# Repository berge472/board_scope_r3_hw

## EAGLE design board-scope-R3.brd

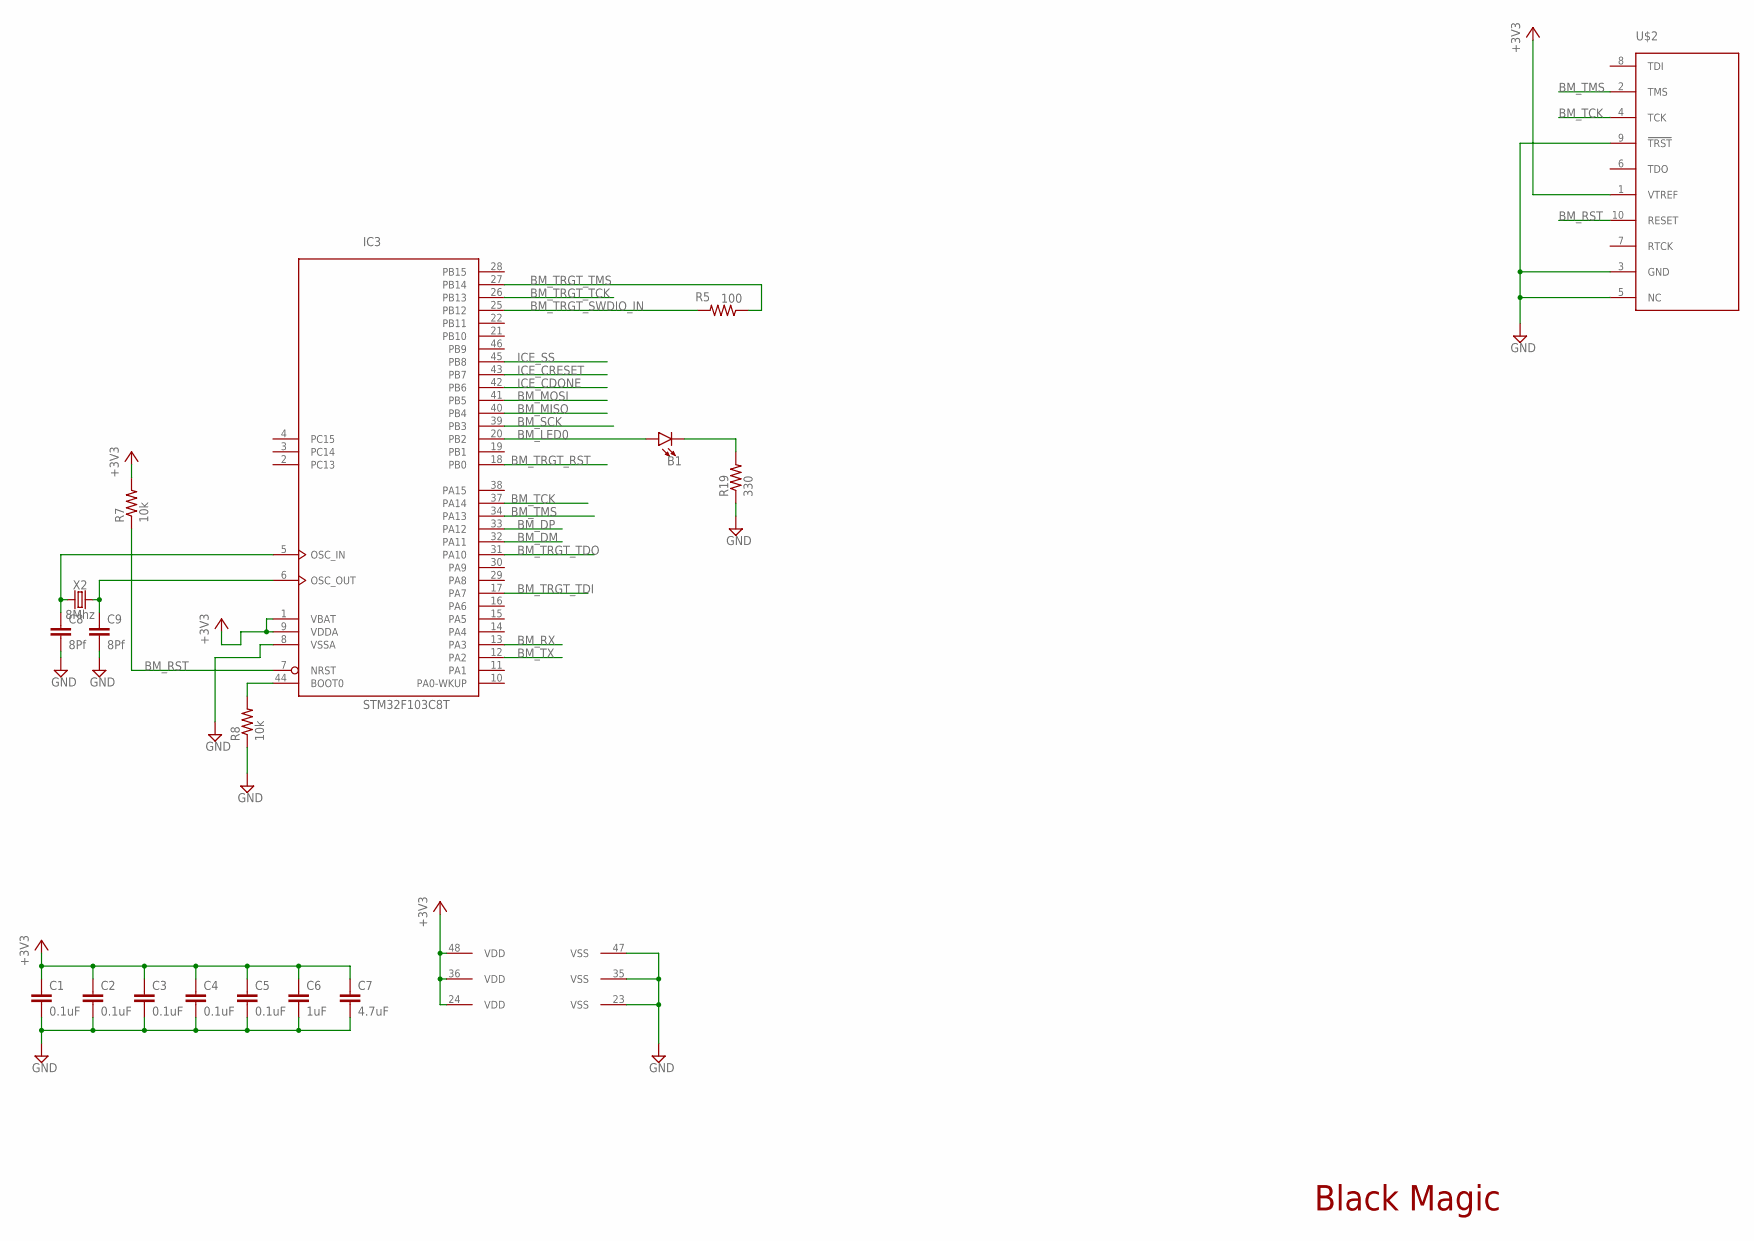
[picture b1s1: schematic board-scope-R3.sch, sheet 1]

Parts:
B1: LED0603; LED-0603
C1, C2, C3, C4, C5: 0.1uF; C0603K
C6: 1uF; C0603K
C7: 4.7uF; C0603K
C8, C9: 8Pf; C0603K
IC3: STM32F103C8T; LQFP48
R5: 100; R0603
R7, R8: 10k; R0603
R19: 330; R0603
U$2: TC2050-NL-MCP-NL; TC2030-MCP-NL
X2: 8Mhz; CRYSTAL-SMD-5X3.2-4PAD

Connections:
+3V3: C1.1, C2.1, C3.1, C4.1, C5.1, C6.1, C7.1, IC3.1 (VBAT), IC3.9 (VDDA), IC3.24 (VDD), IC3.36 (VDD), IC3.48 (VDD), R7.2, U$2.1 (VTREF); also elsewhere on the board
BM_DM: IC3.32 (PA11); also elsewhere on the board
BM_DP: IC3.33 (PA12); also elsewhere on the board
BM_LED0: B1.A, IC3.20 (PB2)
BM_MISO: IC3.40 (PB4); also elsewhere on the board
BM_MOSI: IC3.41 (PB5); also elsewhere on the board
BM_RST: IC3.7 (NRST), R7.1, U$2.10 (RESET); also elsewhere on the board
BM_RX: IC3.13 (PA3); also elsewhere on the board
BM_SCK: IC3.39 (PB3); also elsewhere on the board
BM_TCK: IC3.37 (PA14), U$2.4 (TCK); also elsewhere on the board
BM_TMS: IC3.34 (PA13), U$2.2 (TMS); also elsewhere on the board
BM_TRGT_RST: IC3.18 (PB0); also elsewhere on the board
BM_TRGT_SWDIO_IN: IC3.25 (PB12), R5.2
BM_TRGT_TCK: IC3.26 (PB13); also elsewhere on the board
BM_TRGT_TDI: IC3.17 (PA7); also elsewhere on the board
BM_TRGT_TDO: IC3.31 (PA10); also elsewhere on the board
BM_TRGT_TMS: IC3.27 (PB14), R5.1; also elsewhere on the board
BM_TX: IC3.12 (PA2); also elsewhere on the board
GND: C1.2, C2.2, C3.2, C4.2, C5.2, C6.2, C7.2, C8.2, C9.2, IC3.8 (VSSA), IC3.23 (VSS), IC3.35 (VSS), IC3.47 (VSS), R8.1, R19.1, U$2.3 (GND), U$2.5 (NC), U$2.9 (!TRST); also elsewhere on the board
ICE_CDONE: IC3.42 (PB6); also elsewhere on the board
ICE_CRESET: IC3.43 (PB7); also elsewhere on the board
ICE_SS: IC3.45 (PB8); also elsewhere on the board
unnamed: IC3.44 (BOOT0), R8.2
unnamed: C8.1, IC3.5 (OSC_IN), X2.1
unnamed: C9.1, IC3.6 (OSC_OUT), X2.3 (2)
unnamed: B1.C, R19.2

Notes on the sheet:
Black Magic

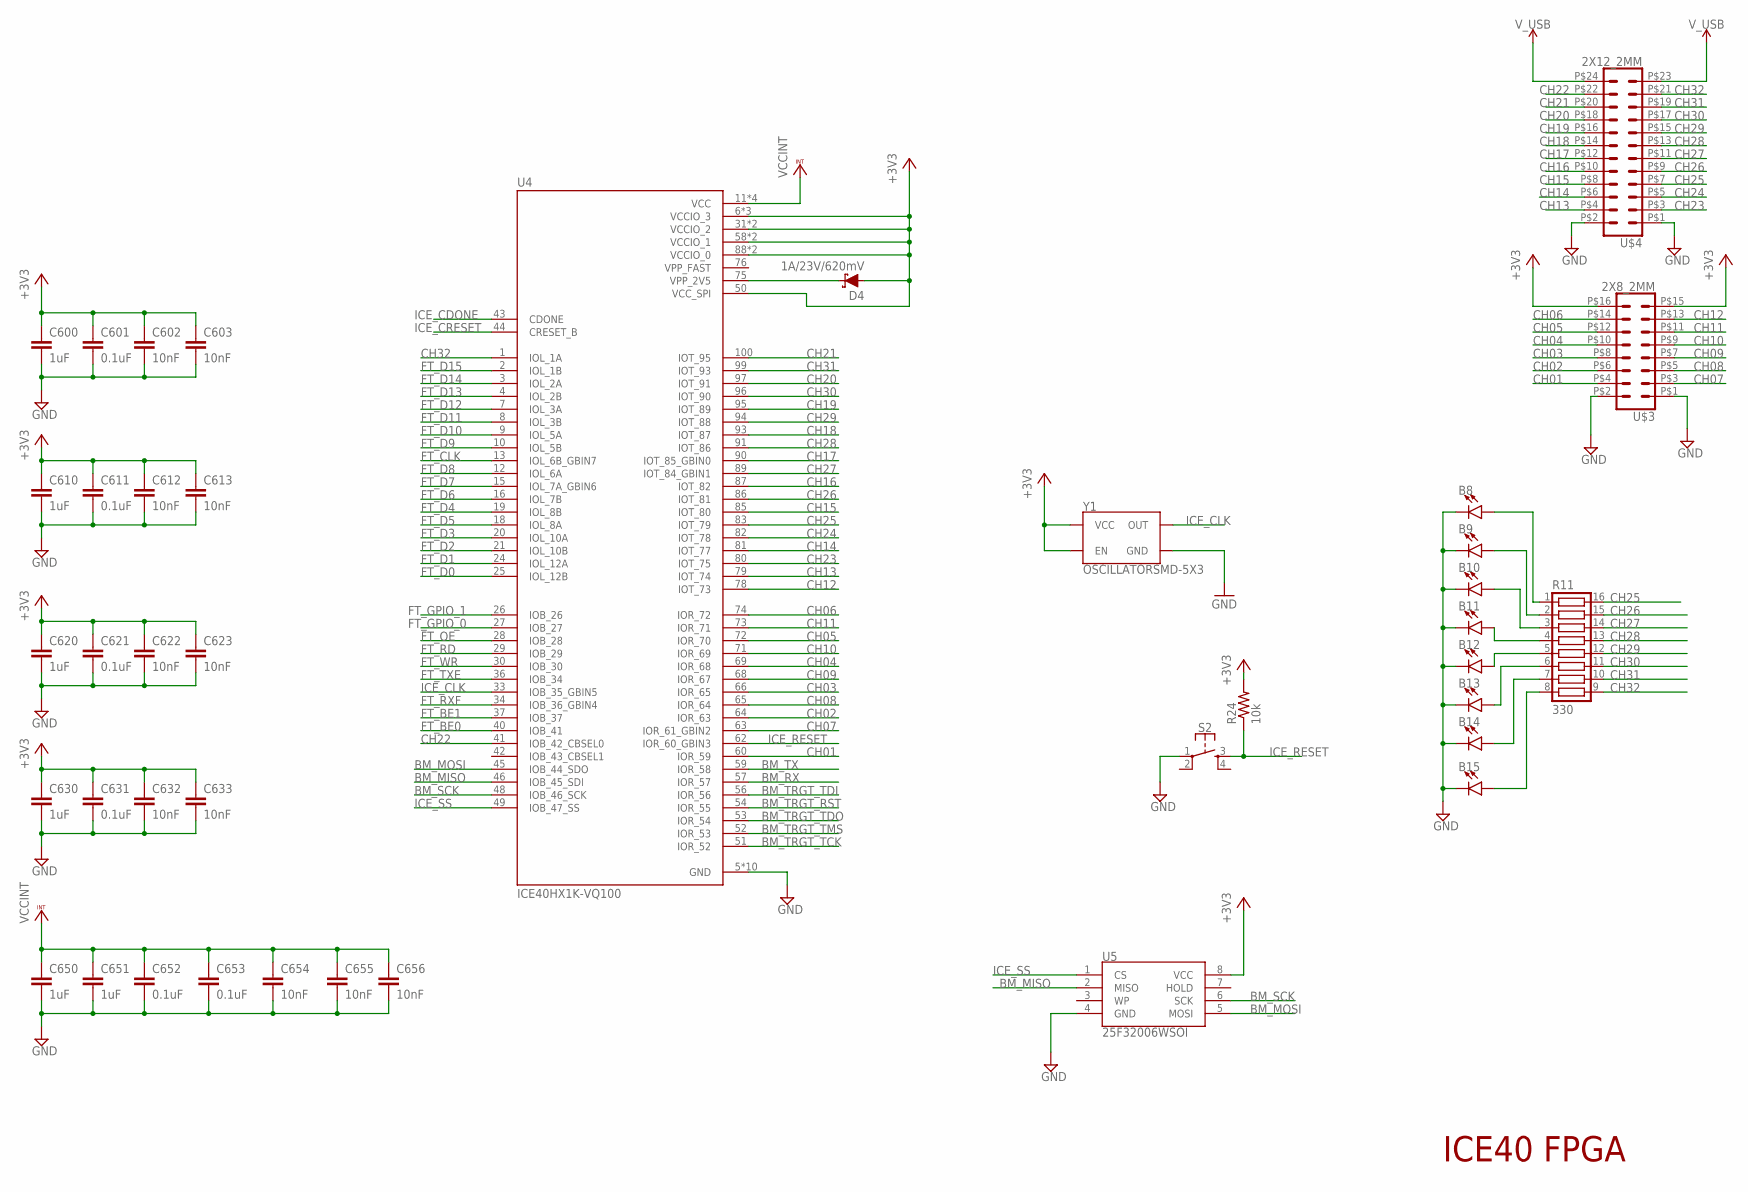
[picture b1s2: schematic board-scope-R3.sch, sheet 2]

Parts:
B8, B9, B10, B11, B12, B13, B14, B15: LED0603; LED-0603
C600, C610, C620, C630, C650, C651: 1uF; C0603K
C601, C611, C621, C631, C652, C653: 0.1uF; C0603K
C602, C603, C612, C613, C622, C623, C632, C633, C654, C655, C656: 10nF; C0603K
D4: 1A/23V/620mV; SOD-323
R11: 330; CTS743C163
R24: 10k; R0603
S2: MOMENTARY-SWITCH-SPST-2-SMD-5.2MM; TACTILE_SWITCH_SMD_5.2MM
U4: ICE40HX1K-VQ100; QFP50P1600X1600X120-100N
U5: 25F32006WSOI; SO08-EIAJ
U$3: 2X8_2MM
U$4: 2X12_2MM
Y1: OSCILLATORSMD-5X3; OSCILLATOR-SMD-5X3.2

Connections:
+3V3: C600.1, C601.1, C602.1, C603.1, C610.1, C611.1, C612.1, C613.1, C620.1, C621.1, C622.1, C623.1, C630.1, C631.1, C632.1, C633.1, D4.A, R24.2, U4.6 (VCCIO_3), U4.14 (VCCIO_3), U4.22 (VCCIO_3), U4.31 (VCCIO_2), U4.38 (VCCIO_2), U4.50 (VCC_SPI), U4.58 (VCCIO_1), U4.67 (VCCIO_1), U4.88 (VCCIO_0), U4.92 (VCCIO_0), U5.8 (VCC), U$3.P$15 (15), U$3.P$16 (16), Y1.1 (EN), Y1.4 (VCC); also elsewhere on the board
BM_MISO: U4.46 (IOB_45_SDI), U5.2 (MISO); also elsewhere on the board
BM_MOSI: U4.45 (IOB_44_SDO), U5.5 (MOSI); also elsewhere on the board
BM_RX: U4.57 (IOR_57); also elsewhere on the board
BM_SCK: U4.48 (IOB_46_SCK), U5.6 (SCK); also elsewhere on the board
BM_TRGT_RST: U4.54 (IOR_55); also elsewhere on the board
BM_TRGT_TCK: U4.51 (IOR_52); also elsewhere on the board
BM_TRGT_TDI: U4.56 (IOR_56); also elsewhere on the board
BM_TRGT_TDO: U4.53 (IOR_54); also elsewhere on the board
BM_TRGT_TMS: U4.52 (IOR_53); also elsewhere on the board
BM_TX: U4.59 (IOR_58); also elsewhere on the board
CH01: U4.60 (IOR_59), U$3.P$4 (4)
CH02: U4.64 (IOR_63), U$3.P$6 (6)
CH03: U4.66 (IOR_65), U$3.P$8 (8)
CH04: U4.69 (IOR_68), U$3.P$10 (10)
CH05: U4.72 (IOR_70), U$3.P$12 (12)
CH06: U4.74 (IOR_72), U$3.P$14 (14)
CH07: U4.63 (IOR_61_GBIN2), U$3.P$3 (3)
CH08: U4.65 (IOR_64), U$3.P$5 (5)
CH09: U4.68 (IOR_67), U$3.P$7 (7)
CH10: U4.71 (IOR_69), U$3.P$9 (9)
CH11: U4.73 (IOR_71), U$3.P$11 (11)
CH12: U4.78 (IOT_73), U$3.P$13 (13)
CH13: U4.79 (IOT_74), U$4.P$4 (4)
CH14: U4.81 (IOT_77), U$4.P$6 (6)
CH15: U4.85 (IOT_80), U$4.P$8 (8)
CH16: U4.87 (IOT_82), U$4.P$10 (10)
CH17: U4.90 (IOT_85_GBIN0), U$4.P$12 (12)
CH18: U4.93 (IOT_87), U$4.P$14 (14)
CH19: U4.95 (IOT_89), U$4.P$16 (16)
CH20: U4.97 (IOT_91), U$4.P$18 (18)
CH21: U4.100 (IOT_95), U$4.P$20 (20)
CH22: U4.41 (IOB_42_CBSEL0), U$4.P$22 (22)
CH23: U4.80 (IOT_75), U$4.P$3 (3)
CH24: U4.82 (IOT_78), U$4.P$5 (5)
CH25: R11.16, U4.83 (IOT_79), U$4.P$7 (7)
CH26: R11.15, U4.86 (IOT_81), U$4.P$9 (9)
CH27: R11.14, U4.89 (IOT_84_GBIN1), U$4.P$11 (11)
CH28: R11.13, U4.91 (IOT_86), U$4.P$13 (13)
CH29: R11.12, U4.94 (IOT_88), U$4.P$15 (15)
CH30: R11.11, U4.96 (IOT_90), U$4.P$17 (17)
CH31: R11.10, U4.99 (IOT_93), U$4.P$19 (19)
CH32: R11.9, U4.1 (IOL_1A), U$4.P$21 (21)
FT_BE0: U4.40 (IOB_41); also elsewhere on the board
FT_BE1: U4.37 (IOB_37); also elsewhere on the board
FT_CLK: U4.13 (IOL_6B_GBIN7); also elsewhere on the board
FT_D0: U4.25 (IOL_12B); also elsewhere on the board
FT_D1: U4.24 (IOL_12A); also elsewhere on the board
FT_D2: U4.21 (IOL_10B); also elsewhere on the board
FT_D3: U4.20 (IOL_10A); also elsewhere on the board
FT_D4: U4.19 (IOL_8B); also elsewhere on the board
FT_D5: U4.18 (IOL_8A); also elsewhere on the board
FT_D6: U4.16 (IOL_7B); also elsewhere on the board
FT_D7: U4.15 (IOL_7A_GBIN6); also elsewhere on the board
FT_D8: U4.12 (IOL_6A); also elsewhere on the board
FT_D9: U4.10 (IOL_5B); also elsewhere on the board
FT_D10: U4.9 (IOL_5A); also elsewhere on the board
FT_D11: U4.8 (IOL_3B); also elsewhere on the board
FT_D12: U4.7 (IOL_3A); also elsewhere on the board
FT_D13: U4.4 (IOL_2B); also elsewhere on the board
FT_D14: U4.3 (IOL_2A); also elsewhere on the board
FT_D15: U4.2 (IOL_1B); also elsewhere on the board
FT_GPIO_0: U4.27 (IOB_27); also elsewhere on the board
FT_GPIO_1: U4.26 (IOB_26); also elsewhere on the board
FT_OE: U4.28 (IOB_28); also elsewhere on the board
FT_RD: U4.29 (IOB_29); also elsewhere on the board
FT_RXF: U4.34 (IOB_36_GBIN4); also elsewhere on the board
FT_TXE: U4.36 (IOB_34); also elsewhere on the board
FT_WR: U4.30 (IOB_30); also elsewhere on the board
GND: B8.C, B9.C, B10.C, B11.C, B12.C, B13.C, B14.C, B15.C, C600.2, C601.2, C602.2, C603.2, C610.2, C611.2, C612.2, C613.2, C620.2, C621.2, C622.2, C623.2, C630.2, C631.2, C632.2, C633.2, C650.2, C651.2, C652.2, C653.2, C654.2, C655.2, C656.2, S2.1, U4.5 (GND), U4.17 (GND), U4.23 (GND), U4.32 (GND), U4.39 (GND), U4.47 (GND), U4.55 (GND), U4.70 (GND), U4.84 (GND), U4.98 (GND), U5.4 (GND), U$3.P$1 (1), U$3.P$2 (2), U$4.P$1 (1), U$4.P$2 (2), Y1.2 (GND); also elsewhere on the board
ICE_CDONE: U4.43 (CDONE); also elsewhere on the board
ICE_CLK: U4.33 (IOB_35_GBIN5), Y1.3 (OUT)
ICE_CRESET: U4.44 (CRESET_B); also elsewhere on the board
ICE_RESET: R24.1, S2.3, U4.62 (IOR_60_GBIN3)
ICE_SS: U4.49 (IOB_47_SS), U5.1 (CS); also elsewhere on the board
unnamed: D4.C, U4.75 (VPP_2V5)
unnamed: B8.A, R11.1
unnamed: B9.A, R11.2
unnamed: B10.A, R11.3
unnamed: B11.A, R11.4
unnamed: B12.A, R11.5
unnamed: B13.A, R11.6
unnamed: B14.A, R11.7
unnamed: B15.A, R11.8
VCCINT: C650.1, C651.1, C652.1, C653.1, C654.1, C655.1, C656.1, U4.11 (VCC), U4.35 (VCC), U4.61 (VCC), U4.77 (VCC); also elsewhere on the board
VPP_FAST: U4.76 (VPP_FAST)
V_USB: U$4.P$23 (23), U$4.P$24 (24); also elsewhere on the board

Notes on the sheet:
ICE40 FPGA

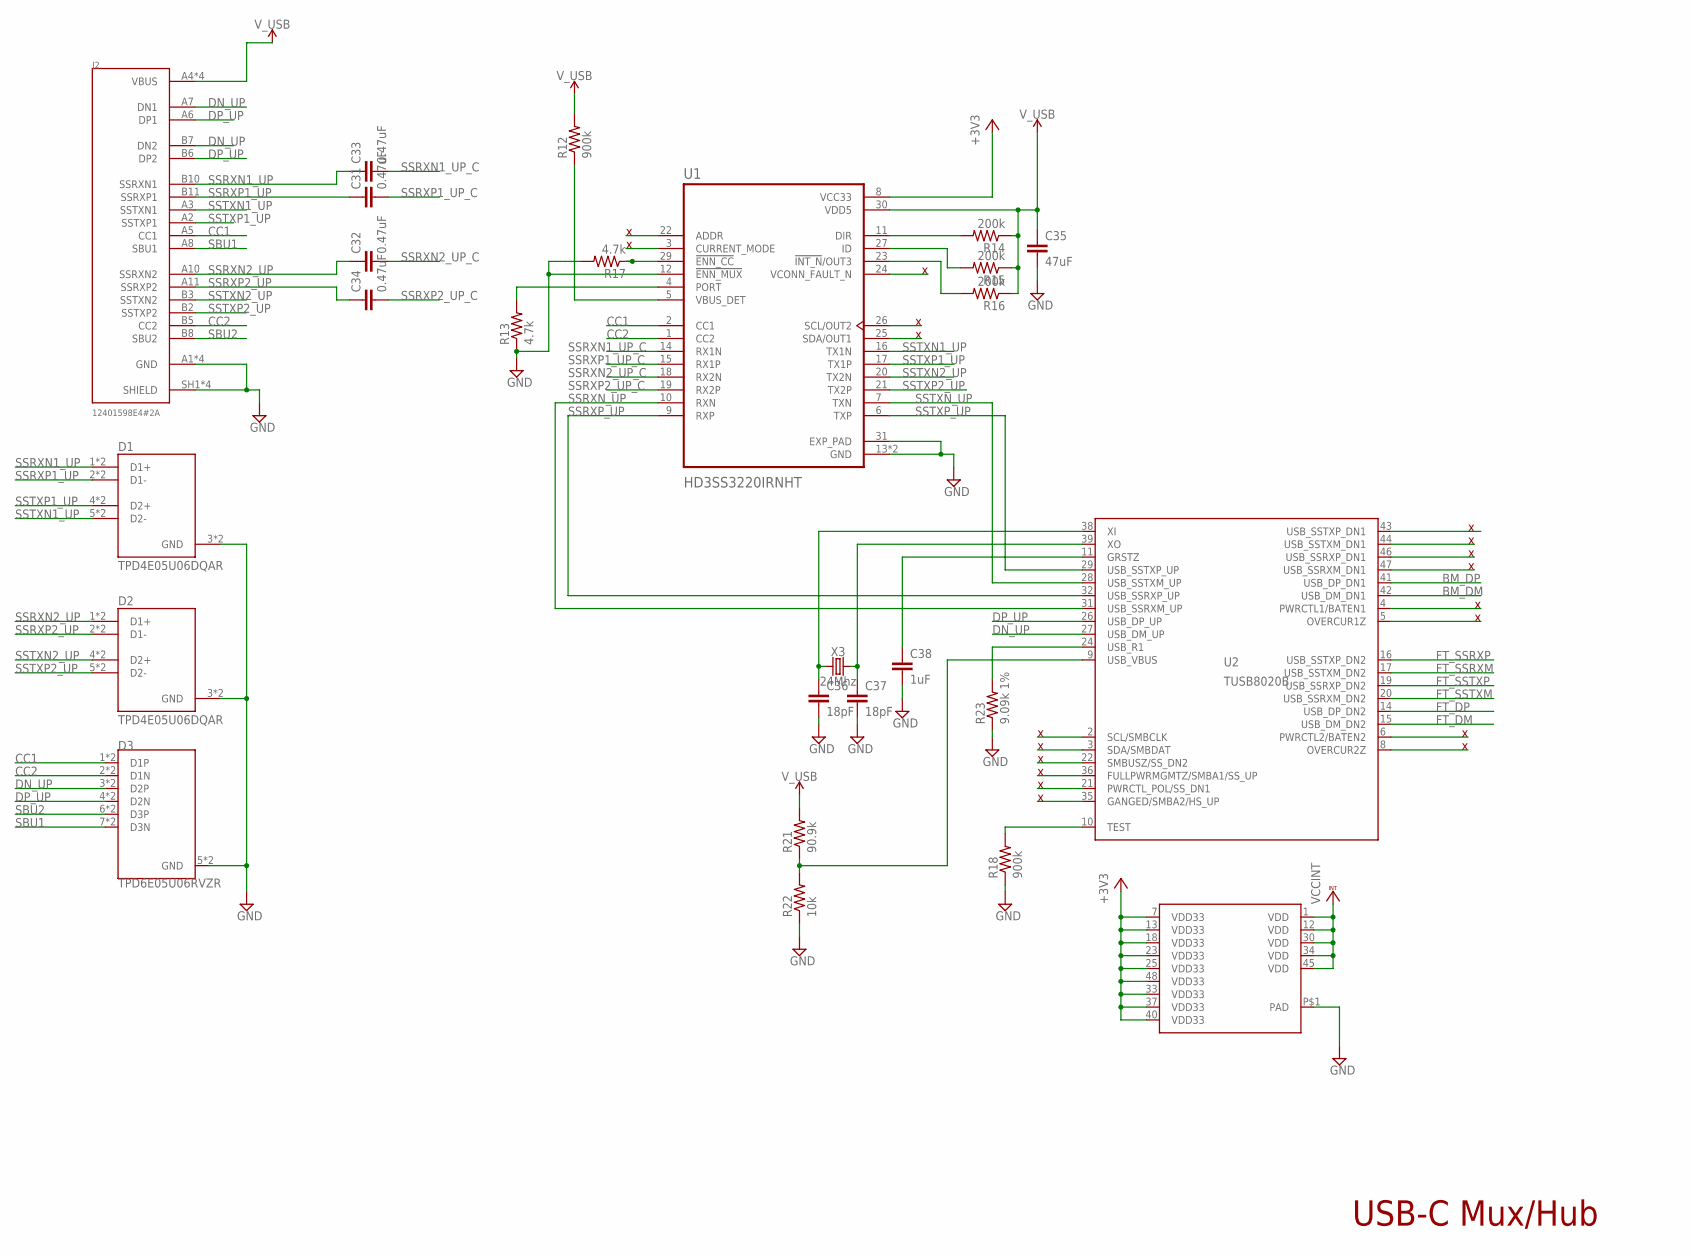
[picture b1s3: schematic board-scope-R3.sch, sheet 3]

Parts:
C31, C32, C33, C34: 0.47uF; C0603K
C35: 47uF; C0603K
C36, C37: 18pF; C0603K
C38: 1uF; C0603K
D1, D2: TPD4E05U06DQAR; TI_TPD4E05U06DQAR
D3: TPD6E05U06RVZR; SON50P135X350X55-14N
J2: 12401598E4#2A; AMPHENOL_12401598E4#2A
R12, R18: 900k; R0603
R13, R17: 4.7k; R0603
R14, R15, R16: 200k; R0603
R21: 90.9k; R0603
R22: 10k; R0603
R23: 9.09k 1%; R0603
U1: HD3SS3220IRNHT; QFN40P450X250X80-31N120X320
U2: TUSB8020B; TQFP48
X3: 24Mhz; CRYSTAL-SMD-5X3.2-4PAD

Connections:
+3V3: U1.8 (VCC33), U2.7 (VDD33), U2.13 (VDD33), U2.18 (VDD33), U2.23 (VDD33), U2.25 (VDD33), U2.33 (VDD33), U2.37 (VDD33), U2.40 (VDD33), U2.48 (VDD33); also elsewhere on the board
BM_DM: U2.42 (USB_DM_DN1); also elsewhere on the board
BM_DP: U2.41 (USB_DP_DN1); also elsewhere on the board
CC1: D3.1 (D1P), D3.14 (D1P), J2.A5 (CC1), U1.2 (CC1)
CC2: D3.2 (D1N), D3.13 (D1N), J2.B5 (CC2), U1.1 (CC2)
DN_UP: D3.3 (D2P), D3.12 (D2P), J2.A7 (DN1), J2.B7 (DN2), U2.27 (USB_DM_UP)
DP_UP: D3.4 (D2N), D3.11 (D2N), J2.A6 (DP1), J2.B6 (DP2), U2.26 (USB_DP_UP)
FT_DM: U2.15 (USB_DM_DN2); also elsewhere on the board
FT_DP: U2.14 (USB_DP_DN2); also elsewhere on the board
FT_SSRXM: U2.17 (USB_SSTXM_DN2); also elsewhere on the board
FT_SSRXP: U2.16 (USB_SSTXP_DN2); also elsewhere on the board
FT_SSTXM: U2.20 (USB_SSRXM_DN2); also elsewhere on the board
FT_SSTXP: U2.19 (USB_SSRXP_DN2); also elsewhere on the board
GND: C35.2, C36.2, C37.2, C38.2, D1.3 (GND), D1.8 (GND), D2.3 (GND), D2.8 (GND), D3.5 (GND), D3.10 (GND), J2.A1 (GND), J2.A12 (GND), J2.B1 (GND), J2.B12 (GND), J2.SH1 (SHIELD), J2.SH2 (SHIELD), J2.SH3 (SHIELD), J2.SH4 (SHIELD), R13.1, R17.2, R18.1, R22.1, R23.1, U1.12 (!ENN_MUX), U1.13 (GND), U1.28 (GND), U1.31 (EXP_PAD), U2.P$1 (PAD); also elsewhere on the board
unnamed: R12.1, U1.5 (VBUS_DET)
unnamed: R13.2, U1.4 (PORT)
unnamed: R15.2, U1.27 (ID)
unnamed: R17.1, U1.29 (!ENN_CC)
unnamed: R14.2, U1.11 (DIR)
unnamed: R16.2, U1.23 (!INT_N!/OUT3)
unnamed: R18.2, U2.10 (TEST)
unnamed: C36.1, U2.38 (XI), X3.1
unnamed: C37.1, U2.39 (XO), X3.3 (2)
unnamed: C38.1, U2.11 (GRSTZ)
unnamed: R21.1, R22.2, U2.9 (USB_VBUS)
unnamed: R23.2, U2.24 (USB_R1)
SBU1: D3.7 (D3N), D3.8 (D3N), J2.A8 (SBU1)
SBU2: D3.6 (D3P), D3.9 (D3P), J2.B8 (SBU2)
SSRXN1_UP: C33.1, D1.1 (D1+), D1.10 (D1+), J2.B10 (SSRXN1)
SSRXN1_UP_C: C33.2, U1.14 (RX1N)
SSRXN2_UP: C32.1, D2.1 (D1+), D2.10 (D1+), J2.A10 (SSRXN2)
SSRXN2_UP_C: C32.2, U1.18 (RX2N)
SSRXN_UP: U1.10 (RXN), U2.31 (USB_SSRXM_UP)
SSRXP1_UP: C31.1, D1.2 (D1-), D1.9 (D1-), J2.B11 (SSRXP1)
SSRXP1_UP_C: C31.2, U1.15 (RX1P)
SSRXP2_UP: C34.1, D2.2 (D1-), D2.9 (D1-), J2.A11 (SSRXP2)
SSRXP2_UP_C: C34.2, U1.19 (RX2P)
SSRXP_UP: U1.9 (RXP), U2.32 (USB_SSRXP_UP)
SSTXN1_UP: D1.5 (D2-), D1.6 (D2-), J2.A3 (SSTXN1), U1.16 (TX1N)
SSTXN2_UP: D2.4 (D2+), D2.7 (D2+), J2.B3 (SSTXN2), U1.20 (TX2N)
SSTXN_UP: U1.7 (TXN), U2.28 (USB_SSTXM_UP)
SSTXP1_UP: D1.4 (D2+), D1.7 (D2+), J2.A2 (SSTXP1), U1.17 (TX1P)
SSTXP2_UP: D2.5 (D2-), D2.6 (D2-), J2.B2 (SSTXP2), U1.21 (TX2P)
SSTXP_UP: U1.6 (TXP), U2.29 (USB_SSTXP_UP)
VCCINT: U2.1 (VDD), U2.12 (VDD), U2.30 (VDD), U2.34 (VDD), U2.45 (VDD); also elsewhere on the board
V_USB: C35.1, J2.A4 (VBUS), J2.A9 (VBUS), J2.B4 (VBUS), J2.B9 (VBUS), R12.2, R14.1, R15.1, R16.1, R21.2, U1.30 (VDD5); also elsewhere on the board

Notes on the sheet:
USB-C Mux/Hub

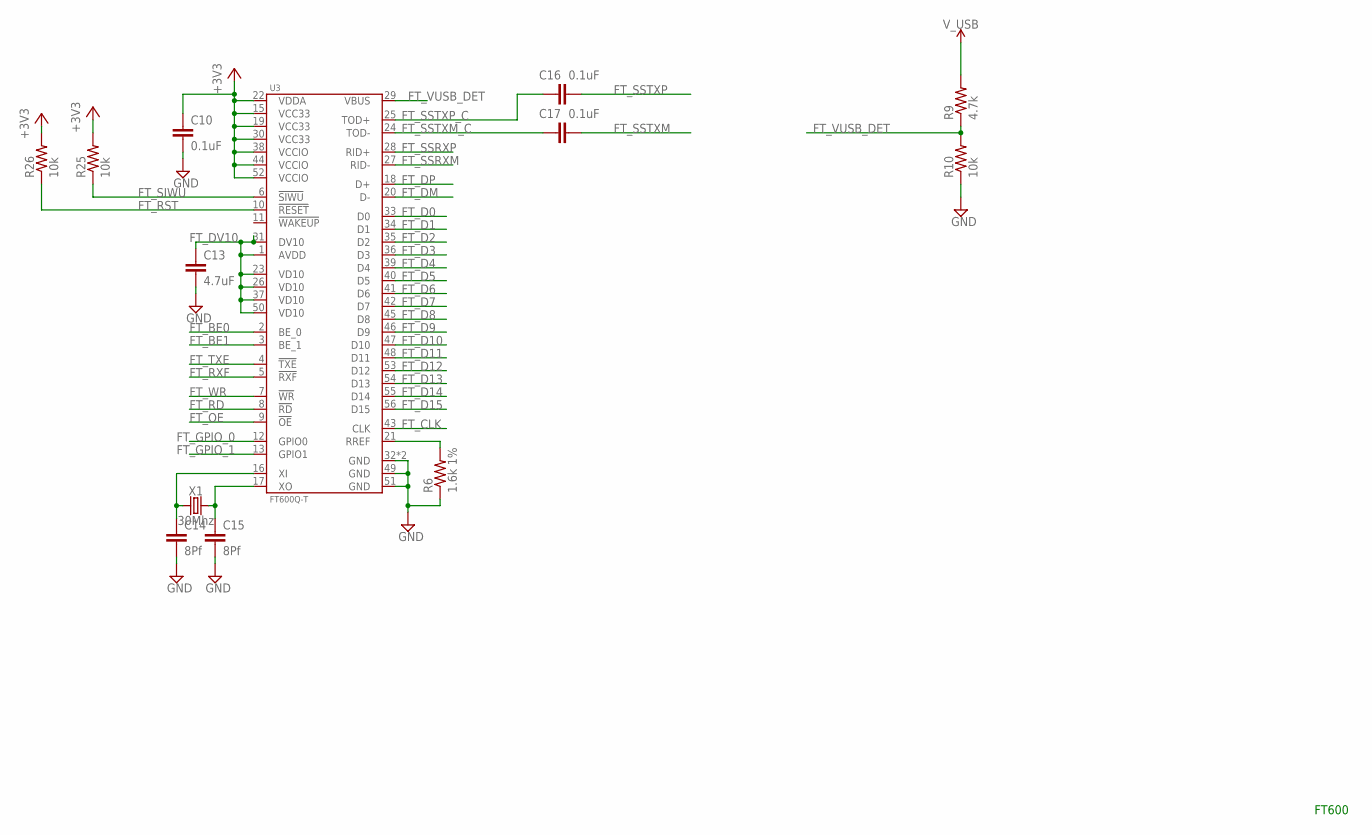
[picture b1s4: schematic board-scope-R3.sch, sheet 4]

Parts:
C10, C16, C17: 0.1uF; C0603K
C13: 4.7uF; C0603K
C14, C15: 8Pf; C0603K
R6: 1.6k 1%; R0603
R9: 4.7k; R0603
R10, R25, R26: 10k; R0603
U3: FT600Q-T; VQFN-56-7MM
X1: 30Mhz; CRYSTAL-SMD-5X3.2-4PAD

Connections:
+3V3: C10.1, R25.2, R26.2, U3.15 (VCC33), U3.19 (VCC33), U3.22 (VDDA), U3.30 (VCC33), U3.38 (VCCIO), U3.44 (VCCIO), U3.52 (VCCIO); also elsewhere on the board
FT_BE0: U3.2 (BE_0); also elsewhere on the board
FT_BE1: U3.3 (BE_1); also elsewhere on the board
FT_CLK: U3.43 (CLK); also elsewhere on the board
FT_D0: U3.33 (D0); also elsewhere on the board
FT_D1: U3.34 (D1); also elsewhere on the board
FT_D2: U3.35 (D2); also elsewhere on the board
FT_D3: U3.36 (D3); also elsewhere on the board
FT_D4: U3.39 (D4); also elsewhere on the board
FT_D5: U3.40 (D5); also elsewhere on the board
FT_D6: U3.41 (D6); also elsewhere on the board
FT_D7: U3.42 (D7); also elsewhere on the board
FT_D8: U3.45 (D8); also elsewhere on the board
FT_D9: U3.46 (D9); also elsewhere on the board
FT_D10: U3.47 (D10); also elsewhere on the board
FT_D11: U3.48 (D11); also elsewhere on the board
FT_D12: U3.53 (D12); also elsewhere on the board
FT_D13: U3.54 (D13); also elsewhere on the board
FT_D14: U3.55 (D14); also elsewhere on the board
FT_D15: U3.56 (D15); also elsewhere on the board
FT_DM: U3.20 (D-); also elsewhere on the board
FT_DP: U3.18 (D+); also elsewhere on the board
FT_DV10: C13.1, U3.1 (AVDD), U3.23 (VD10), U3.26 (VD10), U3.31 (DV10), U3.37 (VD10), U3.50 (VD10)
FT_GPIO_0: U3.12 (GPIO0); also elsewhere on the board
FT_GPIO_1: U3.13 (GPIO1); also elsewhere on the board
FT_OE: U3.9 (!OE); also elsewhere on the board
FT_RD: U3.8 (!RD); also elsewhere on the board
FT_RST: R26.1, U3.10 (!RESET)
FT_RXF: U3.5 (!RXF); also elsewhere on the board
FT_SIWU: R25.1, U3.6 (!SIWU)
FT_SSRXM: U3.27 (RID-); also elsewhere on the board
FT_SSRXP: U3.28 (RID+); also elsewhere on the board
FT_SSTXM: C17.2; also elsewhere on the board
FT_SSTXM_C: C17.1, U3.24 (TOD-)
FT_SSTXP: C16.2; also elsewhere on the board
FT_SSTXP_C: C16.1, U3.25 (TOD+)
FT_TXE: U3.4 (!TXE); also elsewhere on the board
FT_VUSB_DET: R9.1, R10.2, U3.29 (VBUS)
FT_WR: U3.7 (!WR); also elsewhere on the board
GND: C10.2, C13.2, C14.2, C15.2, R6.1, R10.1, U3.32 (GND), U3.49 (GND), U3.51 (GND), U3.PAD (GND); also elsewhere on the board
unnamed: R6.2, U3.21 (RREF)
unnamed: C14.1, U3.16 (XI), X1.1
unnamed: C15.1, U3.17 (XO), X1.3 (2)
V_USB: R9.2; also elsewhere on the board

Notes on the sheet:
FT600

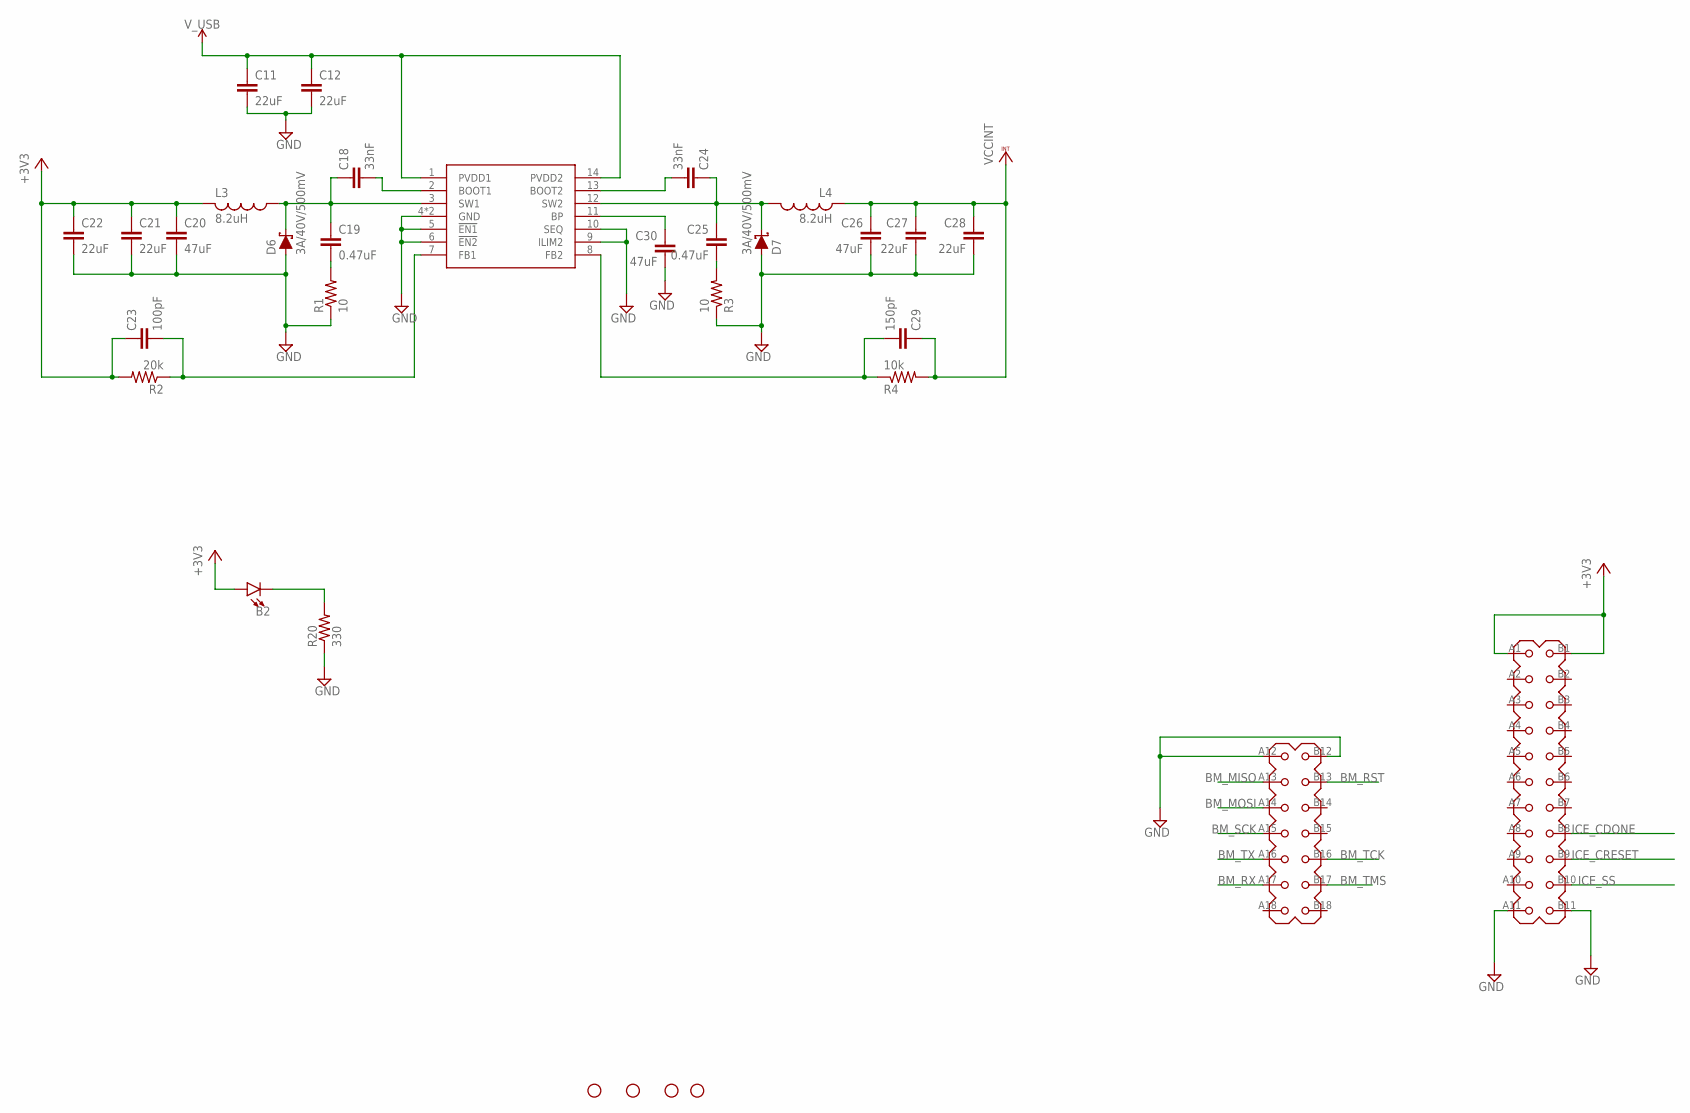
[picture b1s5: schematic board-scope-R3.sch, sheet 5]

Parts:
B2: LED0603; LED-0603
C11, C12, C21, C22, C27, C28: 22uF; C0603K
C18, C24: 33nF; C0603K
C19, C25: 0.47uF; C0603K
C20, C26, C30: 47uF; C0603K
C23: 100pF; C0603K
C29: 150pF; C0603K
D6, D7: 3A/40V/500mV; SMA-DIODE
H1, H2, H3, H4: STAND-OFF
L3, L4: 8.2uH; L5650M
R1, R3: 10; R0603
R2: 20k; R0603
R4: 10k; R0603
R20: 330; R0603
U7: TPS54386; HTSSOP14PWP
U$1: EDGE_DEBUG; PCI-E_36_EDGE_MID

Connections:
+3V3: B2.A, C20.1, C21.1, C22.1, C23.1, L3.2, R2.2, U$1.A1, U$1.B1; also elsewhere on the board
BM_MISO: U$1.A13; also elsewhere on the board
BM_MOSI: U$1.A14; also elsewhere on the board
BM_RST: U$1.B13; also elsewhere on the board
BM_RX: U$1.A17; also elsewhere on the board
BM_SCK: U$1.A15; also elsewhere on the board
BM_TCK: U$1.B16; also elsewhere on the board
BM_TMS: U$1.B17; also elsewhere on the board
BM_TX: U$1.A16; also elsewhere on the board
GND: C11.2, C12.2, C20.2, C21.2, C22.2, C26.2, C27.2, C28.2, C30.2, D6.A, D7.A, R1.1, R3.1, R20.1, U7.4 (GND), U7.5 (!EN1!), U7.6 (!EN2!), U7.9 (ILIM2), U7.10 (SEQ), U7.EXP (GND), U$1.A11, U$1.A12, U$1.B11, U$1.B12; also elsewhere on the board
ICE_CDONE: U$1.B8; also elsewhere on the board
ICE_CRESET: U$1.B9; also elsewhere on the board
ICE_SS: U$1.B10; also elsewhere on the board
unnamed: C18.2, U7.2 (BOOT1)
unnamed: C18.1, C19.1, D6.C, L3.1, U7.3 (SW1)
unnamed: C19.2, R1.2
unnamed: C23.2, R2.1, U7.7 (FB1)
unnamed: C24.2, U7.13 (BOOT2)
unnamed: C24.1, C25.1, D7.C, L4.1, U7.12 (SW2)
unnamed: C25.2, R3.2
unnamed: C29.2, R4.1, U7.8 (FB2)
unnamed: C30.1, U7.11 (BP)
unnamed: B2.C, R20.2
VCCINT: C26.1, C27.1, C28.1, C29.1, L4.2, R4.2; also elsewhere on the board
V_USB: C11.1, C12.1, U7.1 (PVDD1), U7.14 (PVDD2); also elsewhere on the board

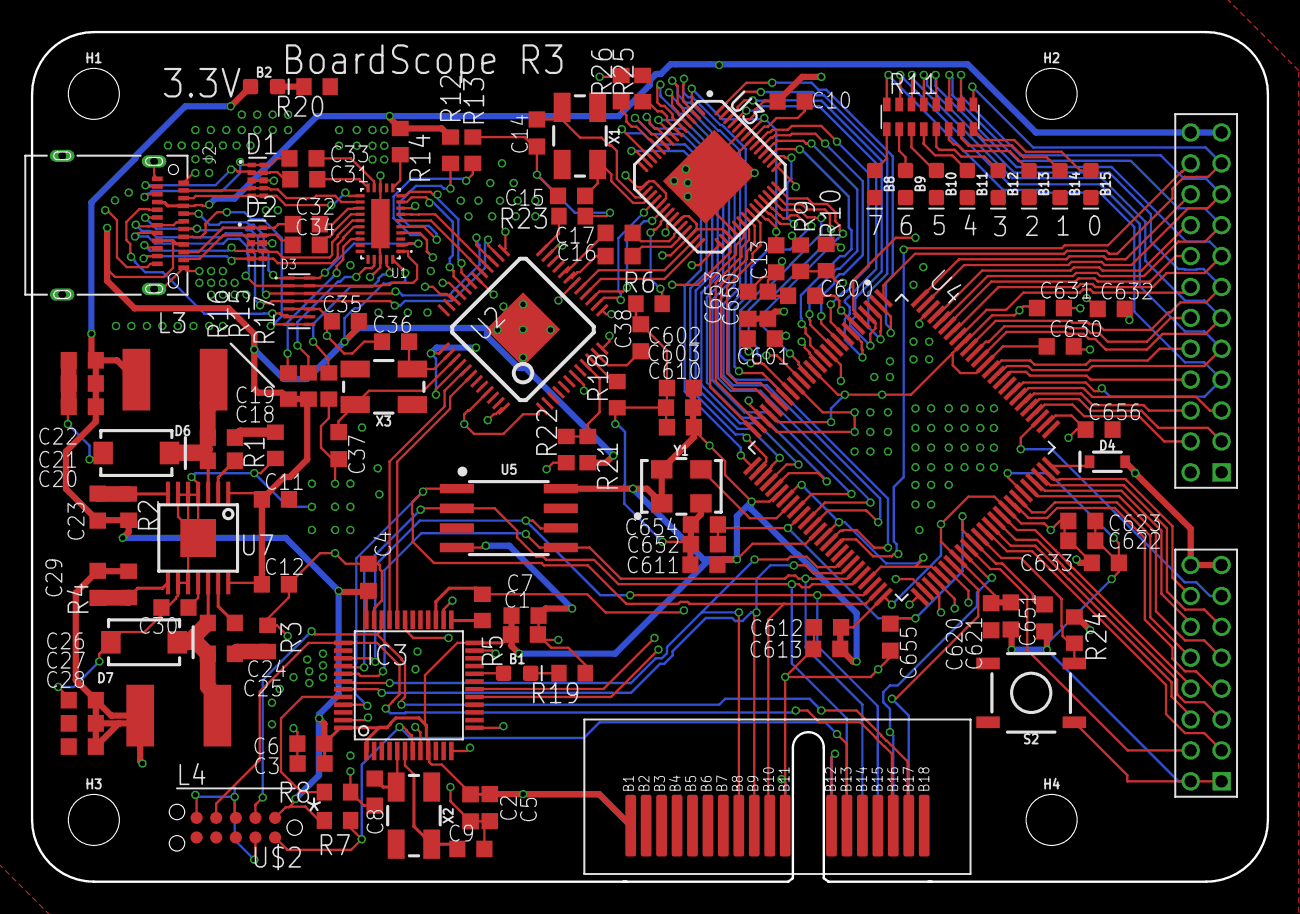
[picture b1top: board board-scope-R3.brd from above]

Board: 4 copper layers, 80.0 x 55.0 mm, 126 parts (0 on the bottom side), 156 nets.

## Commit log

2020-04-11 init
2020-04-11 routed power and usb
2020-04-11 saving
2020-04-12 saving progress
2020-04-12 saving more..
2020-04-12 almost done routing
2020-04-13 done routing
2020-04-13 cleaned up
2020-04-13 submitted..

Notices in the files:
parts and their libraries:
TC2050: ©2009 ROFA.cz
SparkFun-Hardware: Licensing: Creative Commons ShareAlike 4.0 International - https://creativecommons.org/licenses/by-sa/4.0
